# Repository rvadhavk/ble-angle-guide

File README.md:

# BLE Angle Guide

This project is my attempt to create a BLE knife sharpening angle guide/sensor that magnetically clips onto the side of your knife. The UI is a webpage which talks to the sensor using WebBluetooth. The hardware is a custom PCB based around a Panasonic nRF52840 module. The firmware is implemented in Rust using <a href="https://github.com/embassy-rs/embassy">Embassy</a>.  It's my first foray into embedded systems, so the PCB design is probably terrible.

## Project Structure
- [hardware/](./hardware): KiCad files for the PCB
- [firmware/](./firmware): Rust firmware for the nRF52840 module
- [ui/](./ui): Web-based UI (just an index.html file)

## Building the Firmware
The board has 1.27mm/0.05" pitch 2x5 pads which can be connected to using something like <https://www.adafruit.com/product/5434>.  For anyone wanting to develop something similar, a 10 pin connector is unnecessary; all you need is 4 pins: SWCLK, SWDIO, GND, and VCC.

To build and debug, run `cargo run --release` from the `firmware` directory.  Note: the CPU seems to hardfault after some time if running without the `--release` flag.  I haven't figured out why yet; I'm guessing it has to do with a stack overflow.

To flash the device, run `sh flash.sh` from the `firmware` directory.

## UI
The UI is just a single [index.html](./ui/index.html) file.  WebBluetooth requires an https connection, so [development-server.py](./ui/development-server.py) is included for running a simple HTTP server with TLS support.  It requires that `mkcert` be installed or that you manually generate `cert.pem` and `key.pem`.

## Known Issues
- On/off button logic hasn't been implemented yet in the firmware
- USB connector is currently unused in firmware

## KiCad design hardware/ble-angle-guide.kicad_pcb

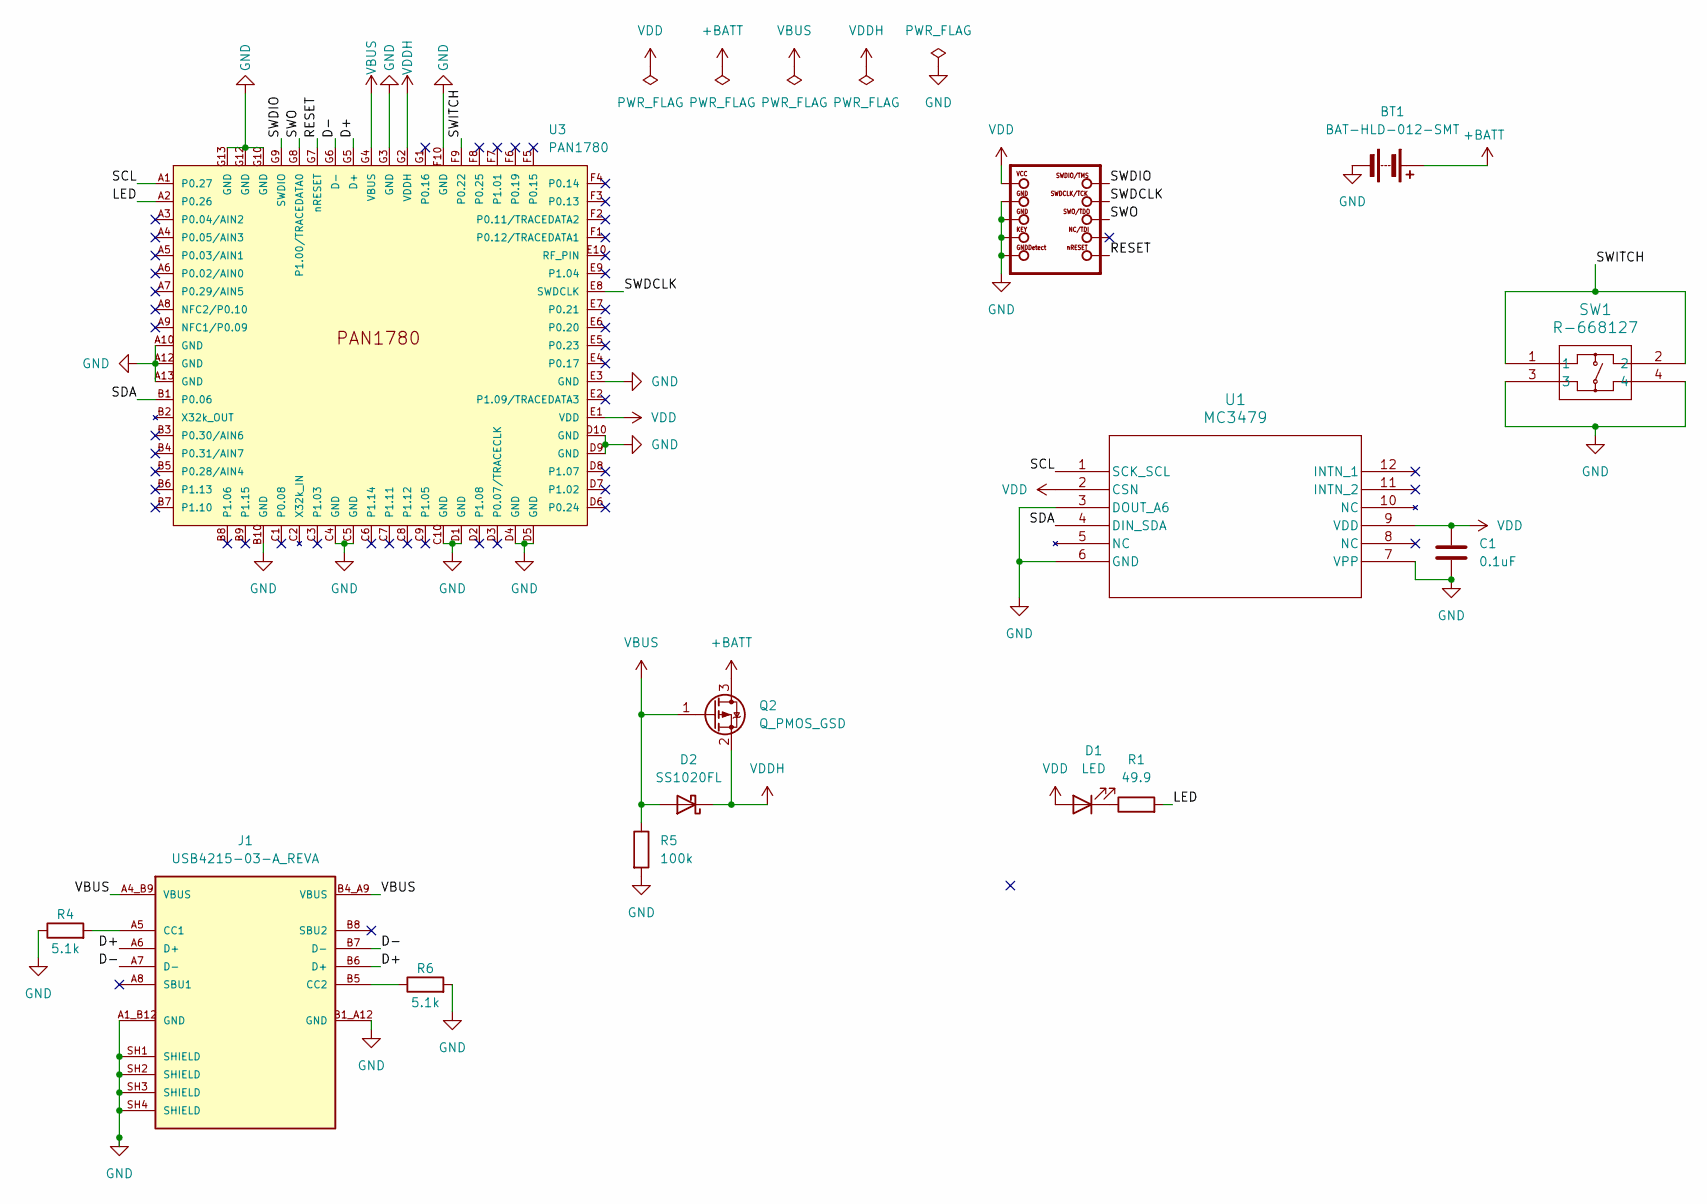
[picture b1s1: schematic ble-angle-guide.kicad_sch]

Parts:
BT1: BAT-HLD-012-SMT; BAT-HLD-012-SMT_TEC
C1: 0.1uF; CAP_CL05_SAM
D1: LED; LED_0402_1005Metric
D2: SS1020FL
J1: USB4215-03-A_REVA; USB4215-03-A_REVA_GCT_USB4215-03-A_REVA; PARTREV A
Q2: Q_PMOS_GSD; SOT-23
R1: 49.9; R_0402_1005Metric
R4, R6: 5.1k; R_0402_1005Metric
R5: 100k; R_0402_1005Metric
SW1: R-668127; R-668127_MIT
SWD2: SWD Contacts
U1: MC3479; MC3479_MEM
U3: PAN1780; PAN1780_PAN1780FP

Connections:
+BATT: BT1.1 (+), Q2.3 (D)
/D+: J1.A6 (D+), J1.B6 (D+), U3.G5 (D+)
/D-: J1.A7 (D-), J1.B7 (D-), U3.G6 (D-)
/LED: R1.2, U3.A2 (P0.26)
/RESET: SWD2.10 (NRESET), U3.G7 (nRESET); also elsewhere on the board
/SCL: U1.1 (SCK_SCL), U3.A1 (P0.27)
/SDA: U1.4 (DIN_SDA), U3.B1 (P0.06)
/SWDCLK: SWD2.4 (SWDCLK), U3.E8 (SWDCLK); also elsewhere on the board
/SWDIO: SWD2.2 (SWDIO), U3.G9 (SWDIO); also elsewhere on the board
/SWITCH: SW1.1, SW1.2, U3.F9 (P0.22)
/SWO: SWD2.6 (SWO), U3.G8 (P1.00/TRACEDATA0); also elsewhere on the board
GND: BT1.2 (-), C1.2, J1.A1_B12 (GND), J1.B1_A12 (GND), J1.SH1 (SHIELD), J1.SH2 (SHIELD), J1.SH3 (SHIELD), J1.SH4 (SHIELD), R4.1, R5.2, R6.2, SW1.3, SW1.4, SWD2.3 (GND@1), SWD2.5 (GND@2), SWD2.7 (KEY), SWD2.9 (GNDDETECT), U1.3 (DOUT_A6), U1.6 (GND), U1.7 (VPP), U3.A10 (GND), U3.A12 (GND), U3.A13 (GND), U3.B10 (GND), U3.C4 (GND), U3.C5 (GND), U3.C10 (GND), U3.D1 (GND), U3.D4 (GND), U3.D5 (GND), U3.D9 (GND), U3.D10 (GND), U3.E3 (GND), U3.F10 (GND), U3.G3 (GND), U3.G10 (GND), U3.G12 (GND), U3.G13 (GND); also elsewhere on the board
unnamed: D1.1 (K), R1.1
unnamed: J1.A5 (CC1), R4.2
unnamed: J1.B5 (CC2), R6.1
VBUS: D2.2 (A), J1.A4_B9 (VBUS), J1.B4_A9 (VBUS), Q2.1 (G), R5.1, U3.G4 (VBUS)
VDD: C1.1, D1.2 (A), SWD2.1 (VCC), U1.2 (CSN), U1.9 (VDD), U3.E1 (VDD); also elsewhere on the board
VDDH: D2.1 (K), Q2.2 (S), U3.G2 (VDDH)

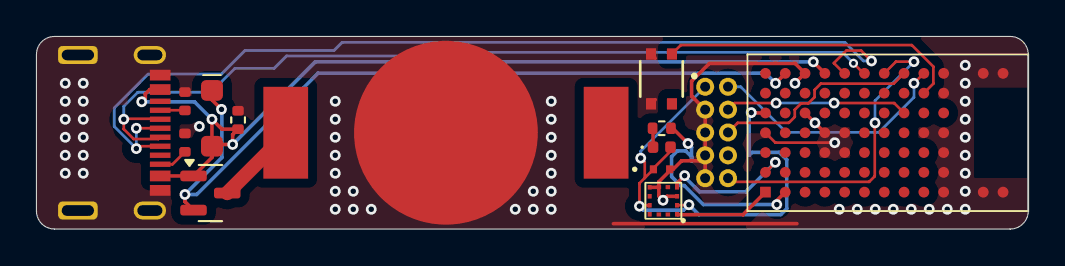
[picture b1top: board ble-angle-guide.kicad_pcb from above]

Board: 2 copper layers, 55.1 x 10.7 mm, 14 parts (0 on the bottom side), 18 nets.

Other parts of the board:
SWD1: SWD Contacts

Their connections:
/RESET: SWD1.10 (NRESET); also elsewhere on the board
/SWDCLK: SWD1.4 (SWDCLK); also elsewhere on the board
/SWDIO: SWD1.2 (SWDIO); also elsewhere on the board
/SWO: SWD1.6 (SWO); also elsewhere on the board
GND: SWD1.3 (GND@1), SWD1.5 (GND@2), SWD1.7 (KEY), SWD1.9 (GNDDETECT); also elsewhere on the board
VDD: SWD1.1 (VCC); also elsewhere on the board

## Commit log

2024-09-27 setup development server
2024-10-04 made the UI more polished
2024-10-04 update dev server script to generate keys if not present. add comments to html
2024-10-04 change name of the rust crate
2024-10-04 fix missing imports in dev server script. add error message for WebBluetooth not supported
2024-10-04 added target angle indicator for other side
2024-10-04 add noscript tag
2024-10-04 added readme and a one line script for flashing
2024-10-05 added screenshot
2024-10-05 Add screenshot to readme
2024-10-05 Fix link to Embassy in readme
2024-10-05 remove extraneous console logs
2024-10-05 Add known issues to readme
